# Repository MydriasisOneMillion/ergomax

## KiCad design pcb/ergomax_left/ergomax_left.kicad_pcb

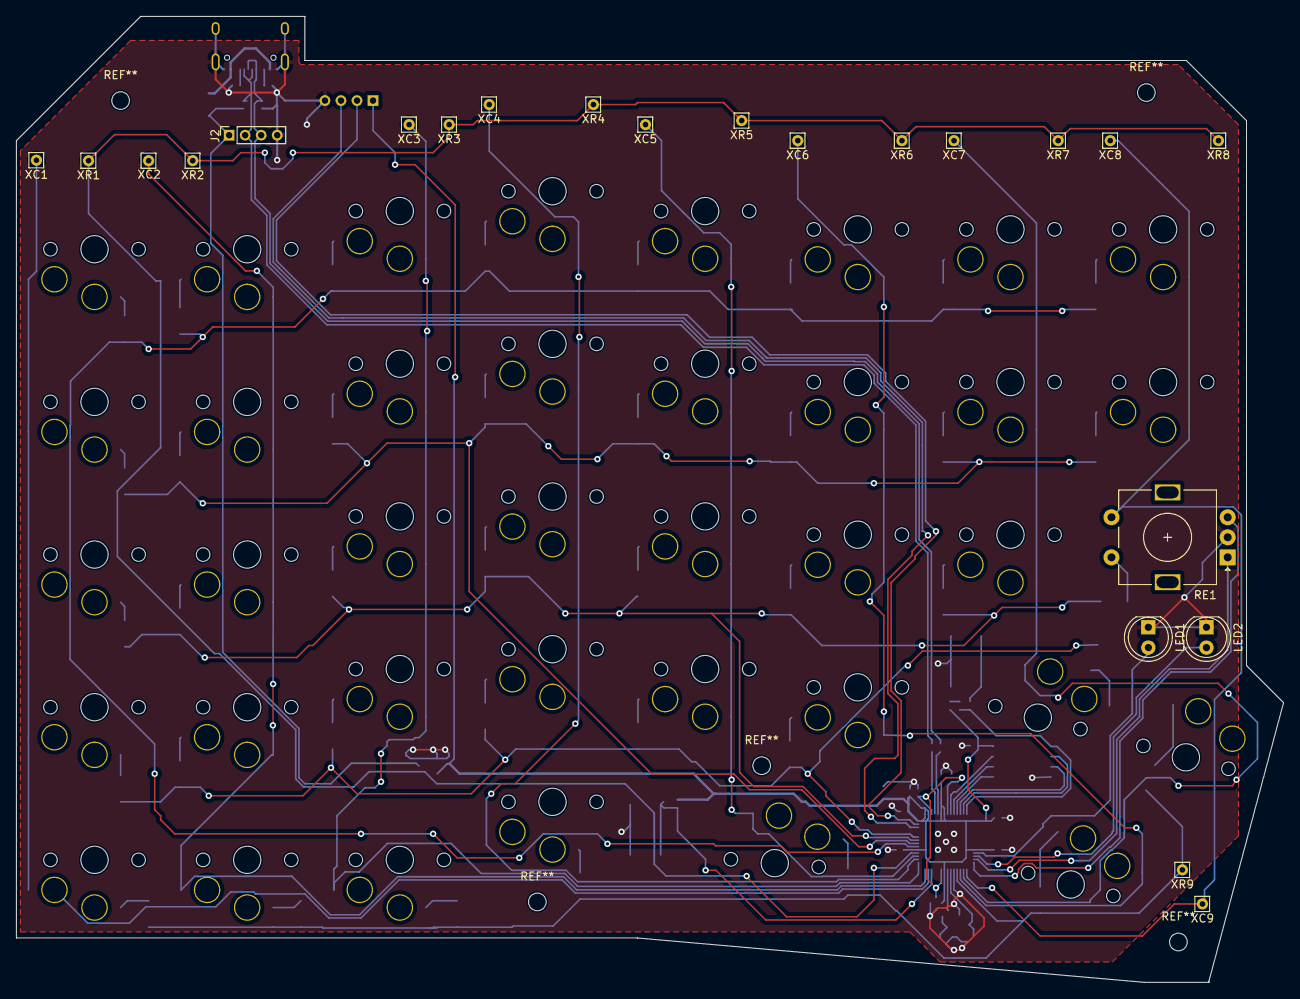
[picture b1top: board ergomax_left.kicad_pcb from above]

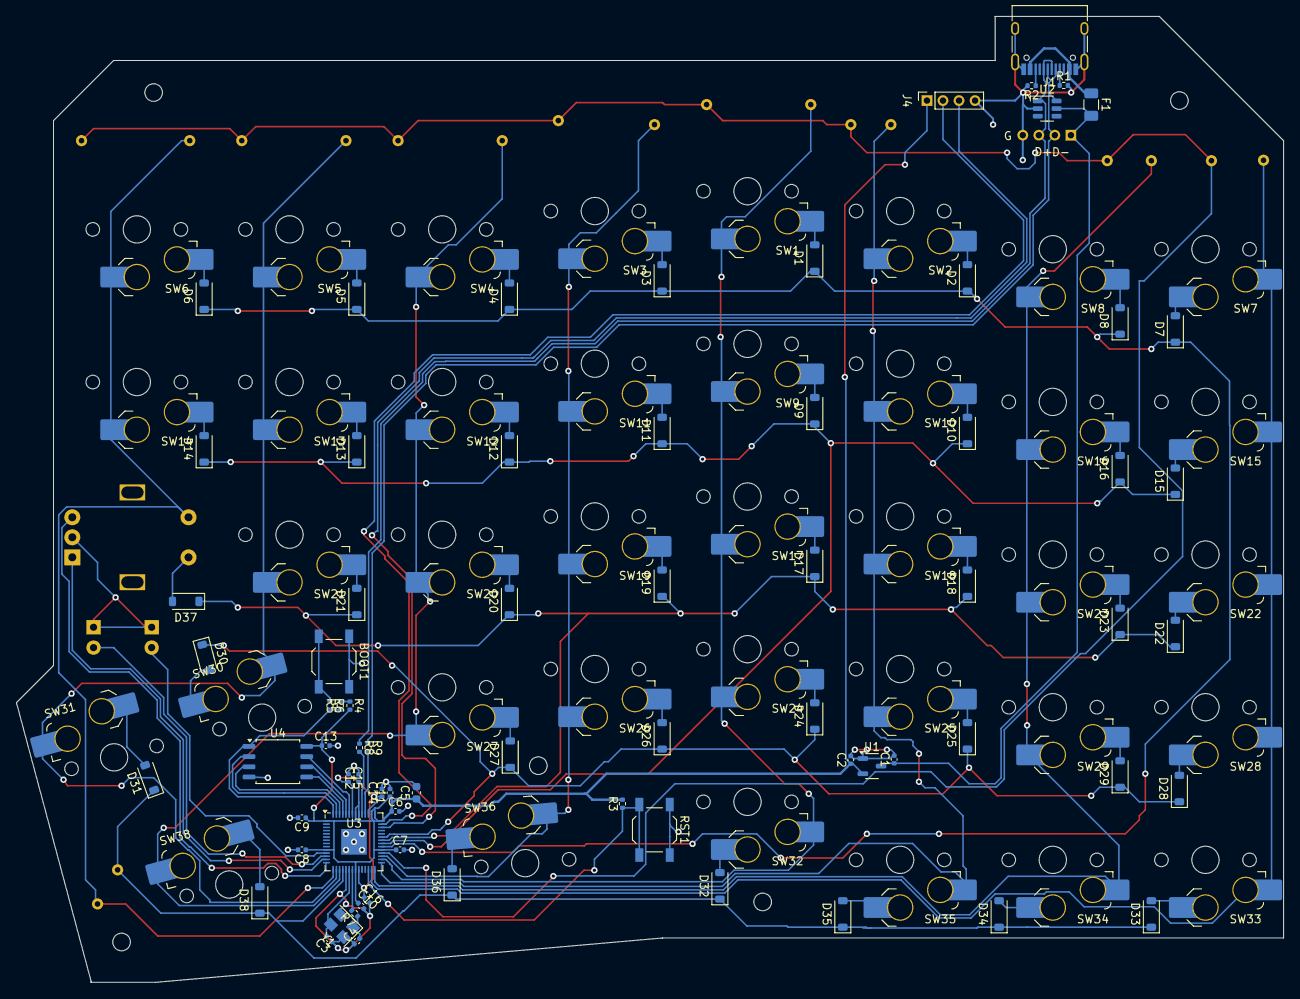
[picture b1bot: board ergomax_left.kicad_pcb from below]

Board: 2 copper layers, 158.1 x 120.5 mm, 132 parts (110 on the bottom side), 81 nets.

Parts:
BOOT1: SW_Push; SW_SPST_TL3342
C1, C2, C6, C13, C14: 1u; C_0402_1005Metric
C3, C4: 22p; C_0402_1005Metric
C5: 10u; C_0603_1608Metric
C7, C8, C9, C10, C11, C12, C15, C16: 100n; C_0402_1005Metric
D1, D2, D3, D4, D5, D6, D7, D8, D9, D10, D11, D12, D13, D14, D15, D16, D17, D18, D19, D20, D21, D22, D23, D24, D25, D26, D27, D28, D29, D30, D31, D32, D33, D34, D35, D36, D37, D38: D_Small; D_SOD-123
F1: Fuse_Small; Fuse_1206_3216Metric
J1: USB_C_Receptacle_USB2.0; USB_C_Receptacle_HRO_TYPE-C-31-M-12
J2: Conn_01x04; PinSocket_1x04_P2.00mm_Vertical
J4: AudioJack4; PinSocket_1x04_P2.00mm_Vertical
LED1, LED2: LED; LED_D5.0mm
R1, R2, R3, R4, R5: 5.1k; R_0402_1005Metric
R6, R7: 1k; R_0402_1005Metric
R8, R9: 27; R_0402_1005Metric
RE1: RotaryEncoder_Switch; RotaryEncoder_Alps_EC11E-Switch_Vertical_H20mm
RST1: SW_Push; SW_SPST_TL3342
SW1, SW2, SW3, SW4, SW5, SW6, SW7, SW8, SW9, SW10, SW11, SW12, SW13, SW14, SW15, SW16, SW17, SW18, SW19, SW20, SW21, SW22, SW23, SW24, SW25, SW26, SW27, SW28, SW29, SW30, SW31, SW32, SW33, SW34, SW35, SW38: MX_SW_HS; SW_choc_v1_HS_CPG135001S30_1u
SW36: MX_SW_HS; SW_choc_v1_HS_CPG135001S30_1.5u
U1: XC6206PxxxMR; SOT-23-3
U2: SRV05-4; SOT-23-6-routable
U3: RP2040; QFN-56-1EP_7x7mm_P0.4mm_EP3.2x3.2mm
U4: W25Q128JVS; SOIC-8_5.23x5.23mm_P1.27mm
XC1, XC2, XC3, XC4, XC5, XC6, XC7, XC8, XC9: Conn_01x01_Pin; Pin_D0.7mm_L6.5mm_W1.8mm_FlatFork
XR1, XR2, XR3, XR4, XR5, XR6, XR7, XR8, XR9: Conn_01x01_Pin; Pin_D0.7mm_L6.5mm_W1.8mm_FlatFork
Y1: Crystal_GND24; Crystal_SMD_3225-4Pin_3.2x2.5mm

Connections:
+1V1: C14.1, C15.2, C16.1, U3.23 (DVDD), U3.45 (VREG_VOUT), U3.50 (DVDD)
+3V3: C2.1, C5.1, C6.1, C7.1, C8.1, C9.1, C10.1, C11.1, C12.1, C13.1, J4.S, R3.2, R4.2, U1.2 (VO), U3.1 (IOVDD), U3.10 (IOVDD), U3.22 (IOVDD), U3.33 (IOVDD), U3.42 (IOVDD), U3.43 (ADC_AVDD), U3.44 (VREG_IN), U3.48 (USB_VDD), U3.49 (IOVDD), U4.8 (VCC)
+5V: C1.1, F1.2, J2.1, U1.3 (VI), U2.5 (VP)
C1: SW7.1, SW15.1, SW22.1, SW28.1, SW33.2, U3.27 (GPIO16), XC1.1
C2: SW8.1, SW16.1, SW23.1, SW29.1, SW34.2, U3.28 (GPIO17), XC2.1
C3: SW2.1, SW10.1, SW18.1, SW25.1, SW35.2, U3.29 (GPIO18), XC3.1
C4: SW1.1, SW9.1, SW17.1, SW24.1, SW32.2, U3.30 (GPIO19), XC4.1
C5: SW3.1, SW11.1, SW19.1, SW26.1, SW36.2, U3.31 (GPIO20), XC5.1
C6: SW4.1, SW12.1, SW20.1, SW27.1, SW38.2, U3.17 (GPIO14), XC6.1
C7: SW5.1, SW13.1, SW21.1, SW30.1, SW31.2, U3.16 (GPIO13), XC7.1
C8: RE1.S1, SW6.1, SW14.1, U3.15 (GPIO12), XC8.1, XC9.1
D+: J1.A6 (D+), J1.B6 (D+), J2.3, R8.1, U2.1 (IO1)
D-: J1.A7 (D-), J1.B7 (D-), J2.2, R9.1, U2.6 (IO4)
GND: BOOT1.1, C1.2, C2.2, C3.1, C4.1, C5.2, C6.2, C7.2, C8.2, C9.2, C10.2, C11.2, C12.2, C13.2, C14.2, C15.1, C16.2, J1.A1 (GND), J1.A12 (GND), J1.B1 (GND), J1.B12 (GND), J1.S1 (SHIELD), J2.4, J4.T, LED1.1 (K), LED2.1 (K), R1.2, R2.2, RE1.C, RST1.1, U1.1 (GND), U2.2 (VN), U3.19 (TESTEN), U3.57 (GND), U4.4 (GND), Y1.2, Y1.4
LED1: LED1.2 (A), U3.11 (GPIO8)
LED2: LED2.2 (A), U3.12 (GPIO9)
unnamed: BOOT1.2, R6.1
unnamed: C4.2, R7.1, Y1.1
unnamed: D1.2 (A), SW1.2
unnamed: D2.2 (A), SW2.2
unnamed: D3.2 (A), SW3.2
unnamed: D4.2 (A), SW4.2
unnamed: D5.2 (A), SW5.2
unnamed: D6.2 (A), SW6.2
unnamed: D7.2 (A), SW7.2
unnamed: D8.2 (A), SW8.2
unnamed: D9.2 (A), SW9.2
unnamed: D10.2 (A), SW10.2
unnamed: D11.2 (A), SW11.2
unnamed: D12.2 (A), SW12.2
unnamed: D13.2 (A), SW13.2
unnamed: D14.2 (A), SW14.2
unnamed: D15.2 (A), SW15.2
unnamed: D16.2 (A), SW16.2
unnamed: D17.2 (A), SW17.2
unnamed: D18.2 (A), SW18.2
unnamed: D19.2 (A), SW19.2
unnamed: D20.2 (A), SW20.2
unnamed: D21.2 (A), SW21.2
unnamed: D22.2 (A), SW22.2
unnamed: D23.2 (A), SW23.2
unnamed: D24.2 (A), SW24.2
unnamed: D25.2 (A), SW25.2
unnamed: D26.2 (A), SW26.2
unnamed: D27.2 (A), SW27.2
unnamed: D28.2 (A), SW28.2
unnamed: D29.2 (A), SW29.2
unnamed: D30.2 (A), SW30.2
unnamed: D31.2 (A), SW31.1
unnamed: D32.2 (A), SW32.1
unnamed: D33.2 (A), SW33.1
unnamed: D34.2 (A), SW34.1
unnamed: D35.2 (A), SW35.1
unnamed: D36.2 (A), SW36.1
unnamed: D37.2 (A), RE1.S2
unnamed: D38.2 (A), SW38.1
unnamed: J1.A5 (CC1), R1.1
unnamed: J1.B5 (CC2), R2.1
unnamed: R4.1, R5.2
unnamed: R9.2, U3.46 (USB_DM)
unnamed: R8.2, U3.47 (USB_DP)
Q_CLK: U3.52 (QSPI_SCLK), U4.6 (CLK)
Q_IO0: U3.53 (QSPI_SD0), U4.5 (DI(IO0))
Q_IO1: U3.55 (QSPI_SD1), U4.2 (DO(IO1))
Q_IO2: U3.54 (QSPI_SD2), U4.3 (IO2)
Q_IO3: U3.51 (QSPI_SD3), U4.7 (IO3)
Q_SEL: R5.1, R6.2, U3.56 (QSPI_SS), U4.1 (~CS)
R1: U3.32 (GPIO21), XR1.1, XR2.1, XR3.1, XR4.1, XR5.1, XR6.1, XR7.1, XR8.1
R2: D1.1 (K), D2.1 (K), D3.1 (K), D4.1 (K), D5.1 (K), D6.1 (K), D7.1 (K), D8.1 (K), U3.34 (GPIO22)
R3: D9.1 (K), D10.1 (K), D11.1 (K), D12.1 (K), D13.1 (K), D14.1 (K), D15.1 (K), D16.1 (K), U3.35 (GPIO23)
R4: D17.1 (K), D18.1 (K), D19.1 (K), D20.1 (K), D21.1 (K), D22.1 (K), D23.1 (K), D37.1 (K), U3.36 (GPIO24)
R5: D24.1 (K), D25.1 (K), D26.1 (K), D27.1 (K), D28.1 (K), D29.1 (K), D30.1 (K), U3.37 (GPIO25)
R6: D31.1 (K), D32.1 (K), D33.1 (K), D34.1 (K), D35.1 (K), D36.1 (K), D38.1 (K), U3.18 (GPIO15), XR9.1
RESET: R3.1, RST1.2, U3.26 (RUN)
RX0: J4.R1, U3.40 (GPIO28_ADC2)
TX0: J4.R2, U3.41 (GPIO29_ADC3)
VBUS: F1.1, J1.A4 (VBUS), J1.A9 (VBUS), J1.B4 (VBUS), J1.B9 (VBUS)
XIN: C3.2, U3.20 (XIN), Y1.3
XOUT: R7.2, U3.21 (XOUT)
en_A: RE1.A, U3.14 (GPIO11)
en_B: RE1.B, U3.13 (GPIO10)

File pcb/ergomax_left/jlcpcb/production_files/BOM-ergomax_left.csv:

Comment,Designator,Footprint,LCSC
1k,"R6,R7",R_0402_1005Metric,C11702
100n,"C10,C11,C12,C15,C16,C7,C8,C9",C_0402_1005Metric,C1525
22p,"C3,C4",C_0402_1005Metric,C1555
USB_C_Receptacle_USB2.0,J1,USB_C_Receptacle_HRO_TYPE-C-31-M-12,C165948
10u,C5,C_0603_1608Metric,C19702
RP2040,U3,QFN-56-1EP_7x7mm_P0.4mm_EP3.2x3.2mm,C2040
27,"R8,R9",R_0402_1005Metric,C25190
5.1k,"R1,R2,R3,R4,R5",R_0402_1005Metric,C25905
1u,"C1,C13,C14,C2,C6",C_0402_1005Metric,C52923
XC6206PxxxMR,U1,SOT-23-3,C5446
Fuse_Small,F1,Fuse_1206_3216Metric,C70076
SRV05-4,U2,SOT-23-6-routable,C7420376
D_Small,"D1,D10,D11,D12,D13,D14,D15,D16,D17,D18,D19,D2,D20,D21,D22,D23,D24,D25,D26,D27,D28,D29,D3,D30,D31,D32,D33,D34,D35,D36,D37,D38,D4,D5,D6,D7,D8,D9",D_SOD-123,C8598
Crystal_GND24,Y1,Crystal_SMD_3225-4Pin_3.2x2.5mm,C9002
W25Q128JVS,U4,SOIC-8_5.23x5.23mm_P1.27mm,C97521

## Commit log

2024-04-24 left draft V1
2024-04-25 post jlcpcb_case info collection
2024-05-13 basic case work
